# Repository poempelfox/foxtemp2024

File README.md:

# FoxTemp 2024

## Intro

The goal of the FoxTemp2024 project is to develop a wireless,
battery powered temperature- and humidity sensor. Wireless in
this case does NOT mean WiFi, but using the 868 MHz ISM band.

This is just the next iteration in a series of very similiar devices, the
previous ones being FoxTemp2022 and FoxTemp2016. The main change
from FoxTemp2022 is that this new iteration does not use
ready made building blocks and just sticks them together,
instead it uses a custom made PCB, designed so that the
design can be sent to a cheap manufacturer that produces
the PCB _and_ already solders most parts on for you.

This project started, because less than a year after constructing
FoxTemp2022 because the parts for FoxTemp2016 were becoming very
painful to source, the main part for FoxTemp2022 (which was a
"Moteino" clone) became unavailable as well.
I then (of course) also wanted a better sensor-chip, namely a
SHT45, but I was unable to find a source for a breakout board
with the 'protective membrane included' variant of
it (SHT45-AD1F). Breakout boards with the other variant
(SHT45-AD1B) were available, but seemed prohibitively expensive
for what they delivered. At the same time, others told me about
chinese PCB prototype assembly manufacturers, that would create
prototypes with the components already soldered on, at
very reasonable prices. I also wanted to finally learn KiCAD.

## Status

In May/June 2024, a "Revision 0" has been designed, targetting
JLCPCB as the manufacturer (meaning it uses parts that that
company had in stock in June 2024), and successfully
produced there. And it actually worked very well.
There is no case-design for this revision.

In August 2024, a "Revision 1" was designed.

## Hardware

The hardware design is very similiar to FoxTemp2022.
At the core is an ATmega328P microcontroller, and the
module used for the 868 MHz wireless link is an
RFM69HW - just like in FoxTemp2022. The main difference
is really that it's all integrated onto a purpose-built
board and manufactured by a factory.

Most parts should already be soldered on, except:
* the RFM69HW needs to be soldered to the back of the board
* a wire antenna needs to be soldered on
* a 3x2 ISP pin header needs to be soldered in
* a battery holder needs to be connected (by soldering on the wires coming from it)

The first of the following picture shows how the boards
looked like when they arrived from the factory. As you can
see, most components are on the front of the board (left
in the picture), and already soldered on. You can also see why
you really would not want to hand-solder the SHT45 - it's
the chip labeled "U2": size 1.5x1.5mm...
The second picture then show the completely assembled thing,
with the handsoldered parts soldered on.

The board has some additional holes for pin headers on the
side that bring out power and unused pins from the
microcontroller. That could e.g. be used to attach additional
sensors. That would naturally require firmware modifications.

Power usage should be pretty low - first measurements show
0.02 mA at 2.8V (this will very much depend on the voltage)
while the device is in deep sleep (which it is most of the
time). Comparing that to FoxTemp2016, it is a bit less,
but on the other hand, the more powerful radio module
will use more power while actually transmitting data.
It is currently completely unknown how long this can
last with one set of batteries, and whether it's longer
or shorter than the roundabout 5 years that FoxTemp2016
managed.

### Revision 1

Revision 1 has the following main changes compared
to Rev. 0:
* XTAL1 was dropped, the internal oscillator of the AVR
  is good enough as we do not do anything timing-critical.
* The battery holder was changed from one attached
  with wires to one that is soldered onto the bottom
  of the board. Due to this, the outline of the PCB and
  the placement of components was changed completely,
  so that it now fits above the battery holder well.
  There is just a small part of the PCB
  protruding over the battery holder, not because more
  space was needed, but because the ISP connectors
  need space on the bottom of the PCB - and there is
  none where the battery holder is tightly clinging
  to the bottom of the PCB
* added alternative TagConnect ISP connector
* The boost converter was changed from a LTC3525 to
  a MAX17224. This should be more efficient and
  thus increase battery life.

## Firmware

The way this was designed, the FoxTemp2022 firmware
simply works without modifications after you set the AVRs
fuses correctly. You can also instead compile the firmware
in Foxtemp2024-mode, that enables some (minor) additional power
savings for FoxTemp2024, but would not work on the FoxTemp2022
hardware.

All firmware development happens in the
[FoxTemp2022 repository](https://github.com/poempelfox/foxtemp2022),
and not here. Just get the firmware from there.

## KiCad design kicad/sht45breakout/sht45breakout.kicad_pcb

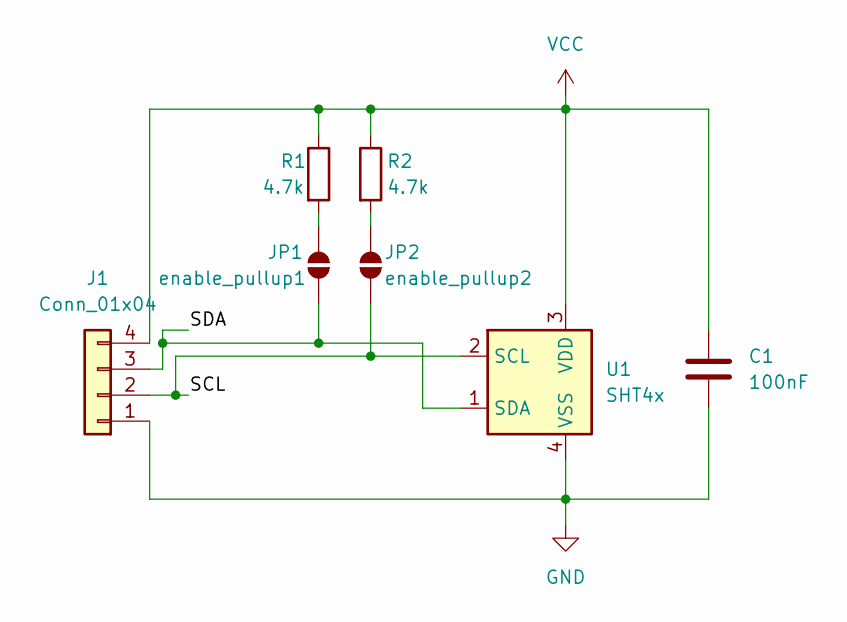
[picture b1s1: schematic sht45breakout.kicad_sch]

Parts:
C1: 100nF; C_0402_1005Metric
J1: Conn_01x04; PinHeader_1x04_P2.54mm_Vertical
JP1: enable_pullup1; SolderJumper-2_P1.3mm_Open_TrianglePad1.0x1.5mm
JP2: enable_pullup2; SolderJumper-2_P1.3mm_Open_TrianglePad1.0x1.5mm
R1, R2: 4.7k; R_0402_modsilkscreen
U1: SHT4x; Sensirion_DFN-4_1.5x1.5mm_P0.8mm_SHT4x_NoCentralPad

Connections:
/SCL: J1.2, JP2.1 (A), U1.2 (SCL)
/SDA: J1.3, JP1.1 (A), U1.1 (SDA)
GND: C1.2, J1.1, U1.4 (VSS)
unnamed: JP1.2 (B), R1.2
unnamed: JP2.2 (B), R2.2
VCC: C1.1, J1.4, R1.1, R2.1, U1.3 (VDD)

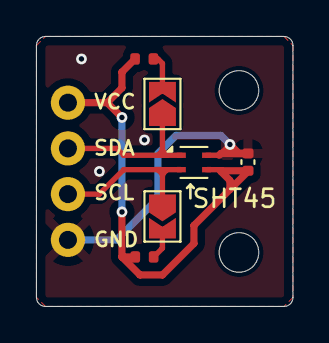
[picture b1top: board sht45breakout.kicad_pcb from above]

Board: 2 copper layers, 14.2 x 15.0 mm, 9 parts (0 on the bottom side), 6 nets.

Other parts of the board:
Hole1, Hole2: MountingHole_2.2mm_M2_DIN965

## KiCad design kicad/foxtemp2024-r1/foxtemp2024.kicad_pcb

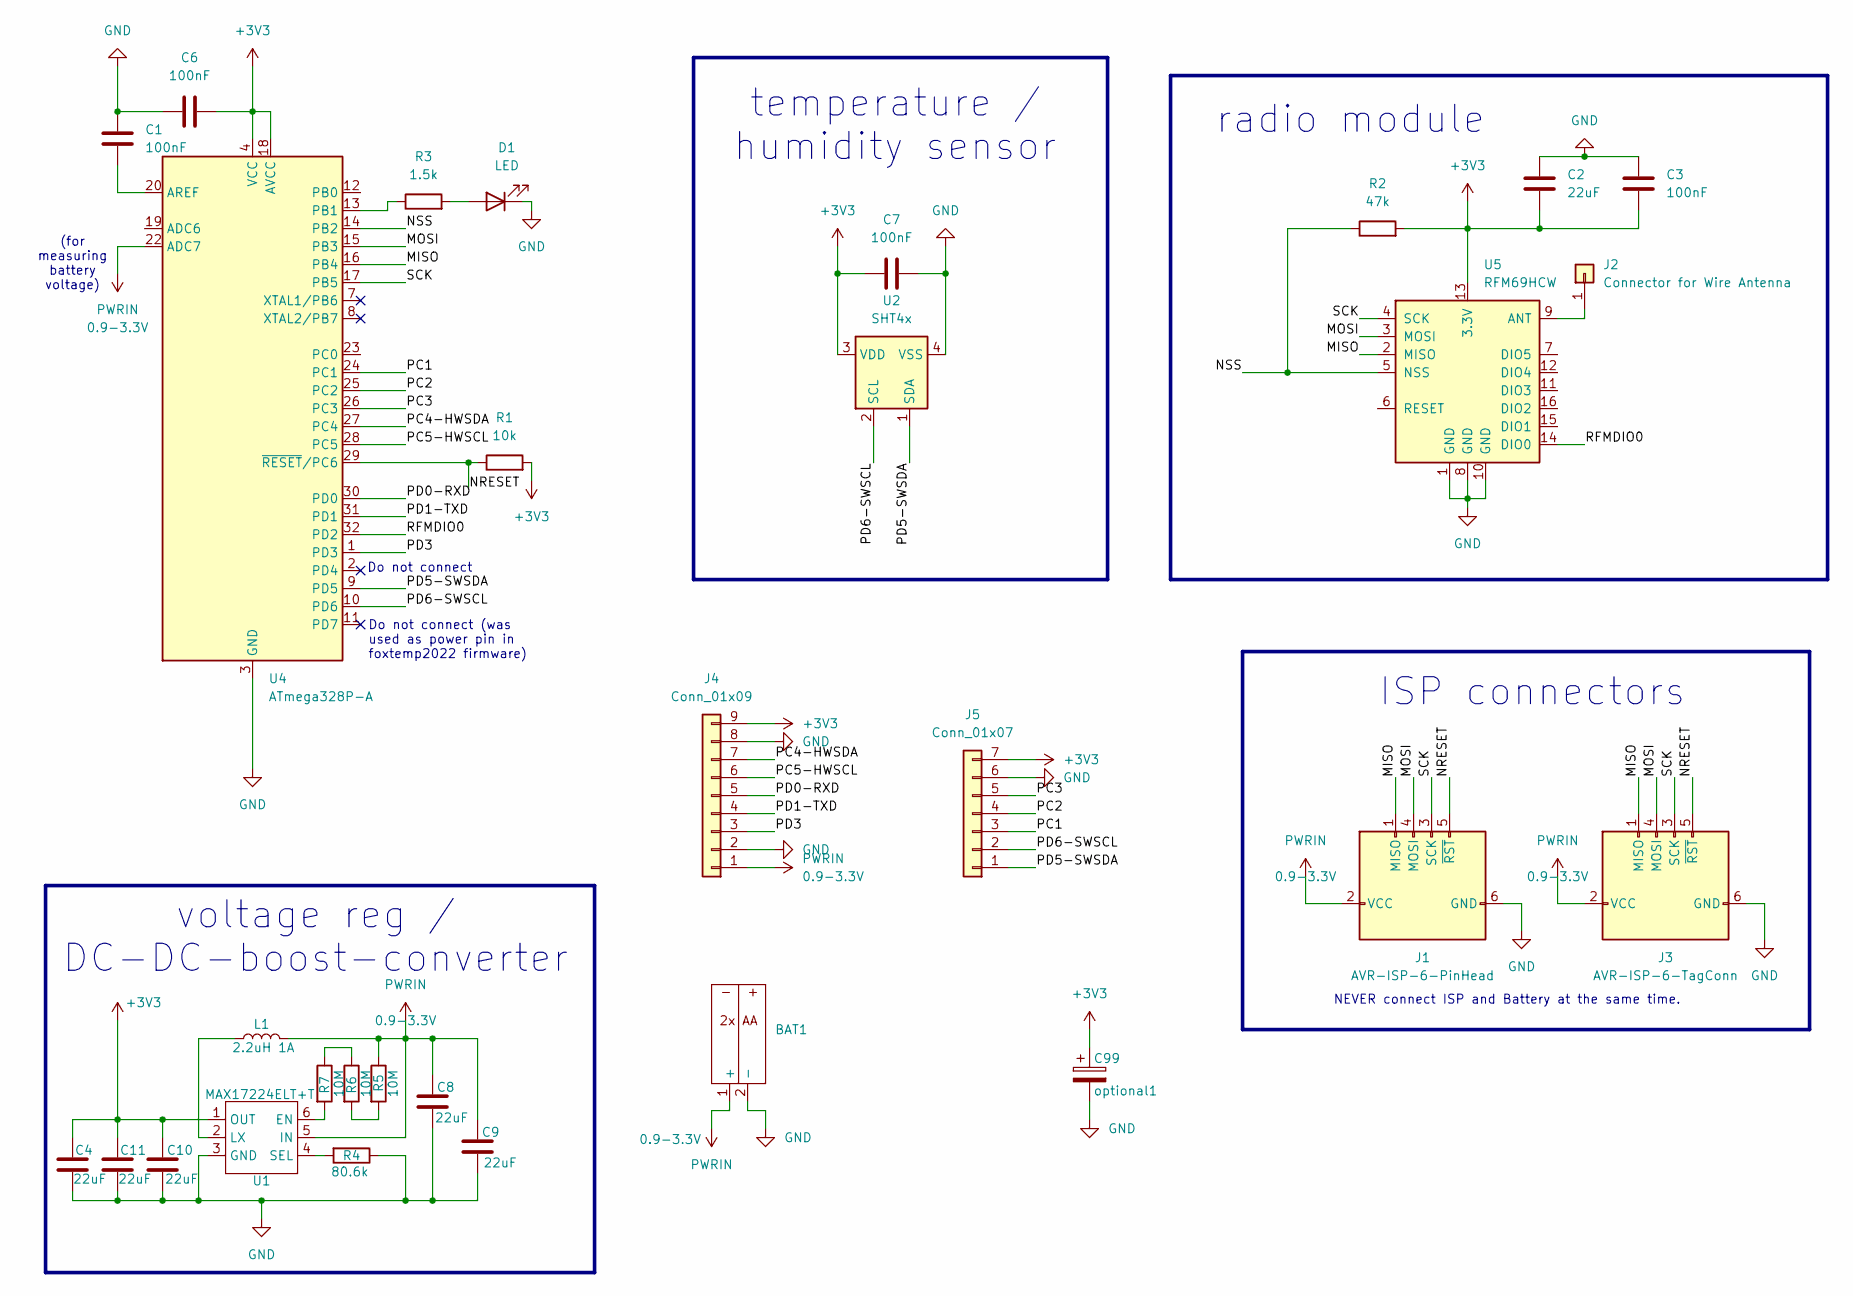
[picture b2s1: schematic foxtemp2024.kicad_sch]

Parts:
BAT1: bathold-keystone-2462
C1, C3, C6, C7: 100nF; C_0402_1005Metric
C2, C4, C8, C9, C10, C11: 22uF; C_0603_1608Metric
C99: optional1; CP_Radial_D6.3mm_P2.50mm
D1: LED; LED_0603_1608Metric
J1: AVR-ISP-6-PinHead; IDC-Header_2x03_P2.54mm_Vertical
J2: Connector for Wire Antenna; PinHeader_1x01_P2.54mm_Vertical
J3: AVR-ISP-6-TagConn; Tag-Connect_TC2030-IDC-FP_2x03_P1.27mm_Vertical
J4: Conn_01x09; PinHeader_1x09_P2.54mm_Vertical
J5: Conn_01x07; PinHeader_1x07_P2.54mm_Vertical
L1: 2.2uH 1A; L_1008_2520Metric
R1: 10k; R_0402_modsilkscreen
R2: 47k; R_0402_modsilkscreen
R3: 1.5k; R_0402_modsilkscreen
R4: 80.6k; R_0402_modsilkscreen
R5, R6, R7: 10M; R_0603_1608Metric
U1: MAX17224ELT+T; UDFN-6_L2.0-W2.0-P0.65-BL-1
U2: SHT4x; Sensirion_DFN-4_1.5x1.5mm_P0.8mm_SHT4x_NoCentralPad
U4: ATmega328P-A; TQFP-32_7x7mm_P0.8mm
U5: RFM69HCW; RFM69HCW-biggerpads

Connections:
+3V3: C2.1, C3.2, C4.1, C6.2, C7.1, C10.1, C11.1, C99.1, J4.9, J5.7, R1.2, R2.2, U1.1 (OUT), U2.3 (VDD), U4.4 (VCC), U4.6 (VCC), U4.18 (AVCC), U5.13 (3.3V)
/MISO: J1.1 (MISO), J3.1 (MISO), U4.16 (PB4), U5.2 (MISO)
/MOSI: J1.4 (MOSI), J3.4 (MOSI), U4.15 (PB3), U5.3 (MOSI)
/NRESET: J1.5 (~RST), J3.5 (~RST), R1.1, U4.29 (~RESET/PC6)
/NSS: R2.1, U4.14 (PB2), U5.5 (NSS)
/PC1: J5.3, U4.24 (PC1)
/PC2: J5.4, U4.25 (PC2)
/PC3: J5.5, U4.26 (PC3)
/PC4-HWSDA: J4.7, U4.27 (PC4)
/PC5-HWSCL: J4.6, U4.28 (PC5)
/PD0-RXD: J4.5, U4.30 (PD0)
/PD1-TXD: J4.4, U4.31 (PD1)
/PD3: J4.3, U4.1 (PD3)
/PD5-SWSDA: J5.1, U2.1 (SDA), U4.9 (PD5)
/PD6-SWSCL: J5.2, U2.2 (SCL), U4.10 (PD6)
/RFMDIO0: U4.32 (PD2), U5.14 (DIO0)
/SCK: J1.3 (SCK), J3.3 (SCK), U4.17 (PB5), U5.4 (SCK)
GND: BAT1.2 (-), C1.1, C2.2, C3.1, C4.2, C6.1, C7.2, C8.2, C9.2, C10.2, C11.2, C99.2, D1.1 (K), J1.6 (GND), J3.6 (GND), J4.2, J4.8, J5.6, R4.1, U1.3 (GND), U2.4 (VSS), U4.3 (GND), U4.5 (GND), U4.21 (GND), U5.1 (GND), U5.8 (GND), U5.10 (GND)
unnamed: D1.2 (A), R3.2
unnamed: J2.1, U5.9 (ANT)
unnamed: R5.2, R6.2
unnamed: R6.1, R7.1
unnamed: R7.2, U1.6 (EN)
unnamed: L1.1, U1.2 (LX)
unnamed: R4.2, U1.4 (SEL)
unnamed: C1.2, U4.20 (AREF)
unnamed: R3.1, U4.13 (PB1)
PWRIN: BAT1.1 (+), C8.1, C9.1, J1.2 (VCC), J3.2 (VCC), J4.1, L1.2, R5.1, U1.5 (IN), U4.22 (ADC7)

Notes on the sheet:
Do not connect
NEVER connect ISP and Battery at the same time.
voltage reg / DC-DC-boost-converter
(for measuring battery voltage)
Do not connect (was used as power pin in foxtemp2022 firmware)
temperature / humidity sensor
radio module
ISP connectors

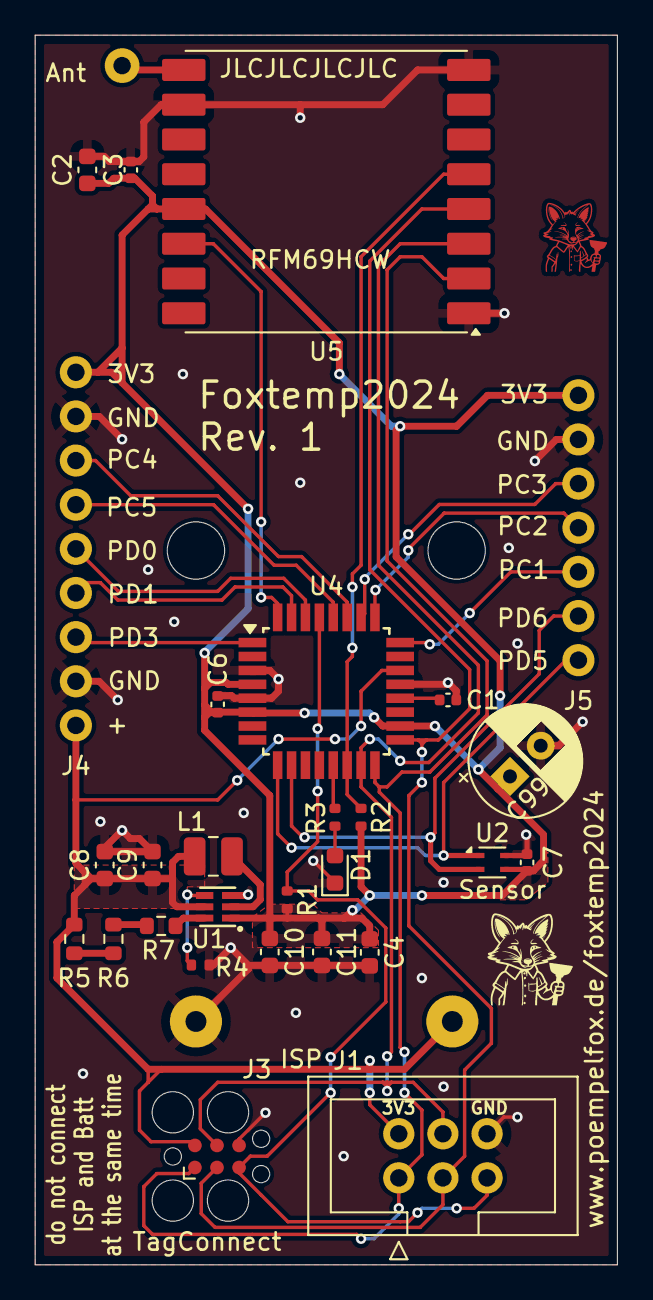
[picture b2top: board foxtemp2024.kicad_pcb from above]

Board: 2 copper layers, 33.5 x 70.8 mm, 30 parts (1 on the bottom side), 28 nets.

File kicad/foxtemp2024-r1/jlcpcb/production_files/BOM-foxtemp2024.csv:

Comment,Designator,Footprint,LCSC
C1,100nF,C_0402_1005Metric,C1525,26786529,0,0
C10,22uF,C_0603_1608Metric,C59461,7095416,0,0
C11,22uF,C_0603_1608Metric,C59461,7095416,0,0
C2,22uF,C_0603_1608Metric,C59461,7095416,0,0
C3,100nF,C_0402_1005Metric,C1525,26786529,0,0
C4,22uF,C_0603_1608Metric,C59461,7095416,0,0
C6,100nF,C_0402_1005Metric,C1525,26786529,0,0
C7,100nF,C_0402_1005Metric,C1525,26786529,0,0
C8,22uF,C_0603_1608Metric,C59461,7095416,0,0
C9,22uF,C_0603_1608Metric,C59461,7095416,0,0
D1,LED,LED_0603_1608Metric,C2286,3092699,0,0
L1,2.2uH 1A,L_1008_2520Metric,C113101,2509,0,0
R1,10k,R_0402_modsilkscreen,C25744,8806732,0,0
R2,47k,R_0402_modsilkscreen,C25792,891377,0,0
R3,1.5k,R_0402_modsilkscreen,C25867,565229,0,0
R4,80.6k,R_0402_modsilkscreen,C25921,21591,0,0
R5,10M,R_0603_1608Metric,C7250,225082,0,0
R6,10M,R_0603_1608Metric,C7250,225082,0,0
R7,10M,R_0603_1608Metric,C7250,225082,0,0
U1,MAX17224ELT+T,UDFN-6_L2.0-W2.0-P0.65-BL-1,C2683469,139,0,0
U2,SHT4x,Sensirion_DFN-4_1.5x1.5mm_P0.8mm_SHT4x_NoCentralPad,C5360602,2016,0,0
U4,ATmega328P-A,TQFP-32_7x7mm_P0.8mm,C14877,19962,0,0

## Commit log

2024-06-02 initial iteration, as it will probably be sent for fabrication.
2024-06-02 production files Rev. 0 for JLCPCB, as ordered from JLCPCB.
2024-06-02 simple SHT45 breakout board this does not really have much to do with foxtemp2024, except that it uses the same chip and was constructed concurrently with that and is too small a project to justify i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
2024-06-08 start readme
2024-06-13 update status
2024-06-14 rename directory so that the name contains the revision
2024-06-15 a bit of info on power usage
2024-06-15 a little more text and another picture of the fully assembled thing.
2024-06-15 add schematics pdf, so you can have a look without having to open kicad.
2024-08-18 add Revision 1
2024-08-18 update README with current status
2024-08-23 revision 1 as sent to JLCPCB for production
2024-08-23 add 4.7k pullup resistors and solder jumpers to enable them (by default they are disabled)
